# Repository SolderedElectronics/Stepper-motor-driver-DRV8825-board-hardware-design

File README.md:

# Stepper motor driver DRV8825 board Hardware Design

## About the Product

|  |
| :----------------------------------------------------------: |
| [Buy Stepper motor driver DRV8825 board](https://www.solde.red/333000) |

The stepper motor driver enables very precise control of the stepper motor. The DRV8825, located on this board, enables microstepping of a bipolar motor with an adjustable current limit, overcurrent and overtemperature protection. Controls steps up to 1/32 step. It has a potentiometer for setting the desired current.

---

## Repository Contents

This repository contains all design files for Stepper motor driver DRV8825 board, organized as follows:

- **`CAD` folder**: Contains KiCAD design files, including:
  - Schematics
  - PCB layout
  - Panel PCB layout
  - Source 3D files in Fusion360, if any
  - All files are sorted by version with a detailed change log.
- **`OUTPUTS` folder**: Includes all production-ready files, such as:
  - Bill of Materials (BOM) and interactive BOM (iBOM)
  - PDF versions of schematics
  - 3D `.step` file of the board
  - 3D-printable models
  - Gerber files for PCB manufacturing
  - Image of the pinout of the board
  - Product image
  - Compliance, legal and generic sales documents

Refer to the `Change Log` in the CAD folder for details about updates between versions.

---

## Learn More About the Product

Beyond the repository, explore the following resources:

### Soldered Verify

The **Soldered Verify** system ensures every board you purchase from Soldered is fully functional. It also provides access to exclusive test data for your product. To get started, find the unique Soldered Verify ID on your product's packaging and enter the ID on the [Soldered Verify page](https://soldered.com/verify/) to access test results and additional product details.

### Soldered Community

Soldered Community is your go-to place for technical support. Our engineers track and answer all questions posted there, and it’s a great space for the maker community. Get answers to your questions and solutions for your challenges at [Soldered Community](https://soldered.com/community).

### solde.red

solde.red is an ultimate URL shortener and information hub. Access it by typing solde.red/ followed by your product SKU, e.g., [solde.red/333000](https://solde.red/333000), to find getting-started guides, datasheets, open-source hardware and software files, certifications, images, pinouts, and more. Read more about the shortener [here](https://solde.red/info/).

---

## Contributing

Contributions are welcome! Here’s how you can get involved:

- Submit pull requests to enhance the design or fix issues.
- Report bugs or problems by opening an issue.

We encourage community collaboration to make this product even better.

---

## About Soldered

[Soldered for Makers](https://soldered.com) specializes in designing and manufacturing electronic products tailored for enthusiasts, ranging from hobbyists to professionals. Our portfolio includes electronic boards, sensors, and actuators that are widely utilized in fields such as microelectronics, mechatronics, robotics, programming, and IoT. Every product we offer is designed in-house and built upon open-source hardware and software platforms. Proudly certified and manufactured within the European Union, our catalog likely includes the product you need for your project.

We complement these products with comprehensive tutorials and manuals, product descriptions, schematics, programming codes, and project examples. Our round-the-clock [customer and technical support](https://soldered.com/community) is available for all our products, irrespective of the sales channel. Soldered’s success and services reflect our maker community’s unwavering [trust](https://www.trustpilot.com/review/soldered.com), for which we are deeply grateful. Join our community and create using Soldered products.

---

## License

All Soldered open-source hardware (OSH) is under The TAPR Open Hardware License. Read more in the LICENSE file located in this repository.

**Disclaimer:**

No warranty - all designs in this repository are distributed in the hope that they will be useful, but without any warranty. They are provided "AS IS", therefore without warranty of any kind, either expressed or implied. The entire quality and performance of what you do with the contents of this repository are your responsibility. In no event Soldered Electronics will be liable for your damages, or losses, including any general, special, incidental, or consequential damage arising out of the use or inability to use the contents of this repository. 

---

## Have fun!

Thank you for your support from your fellow makers at Soldered Electronics.

Happy Making!

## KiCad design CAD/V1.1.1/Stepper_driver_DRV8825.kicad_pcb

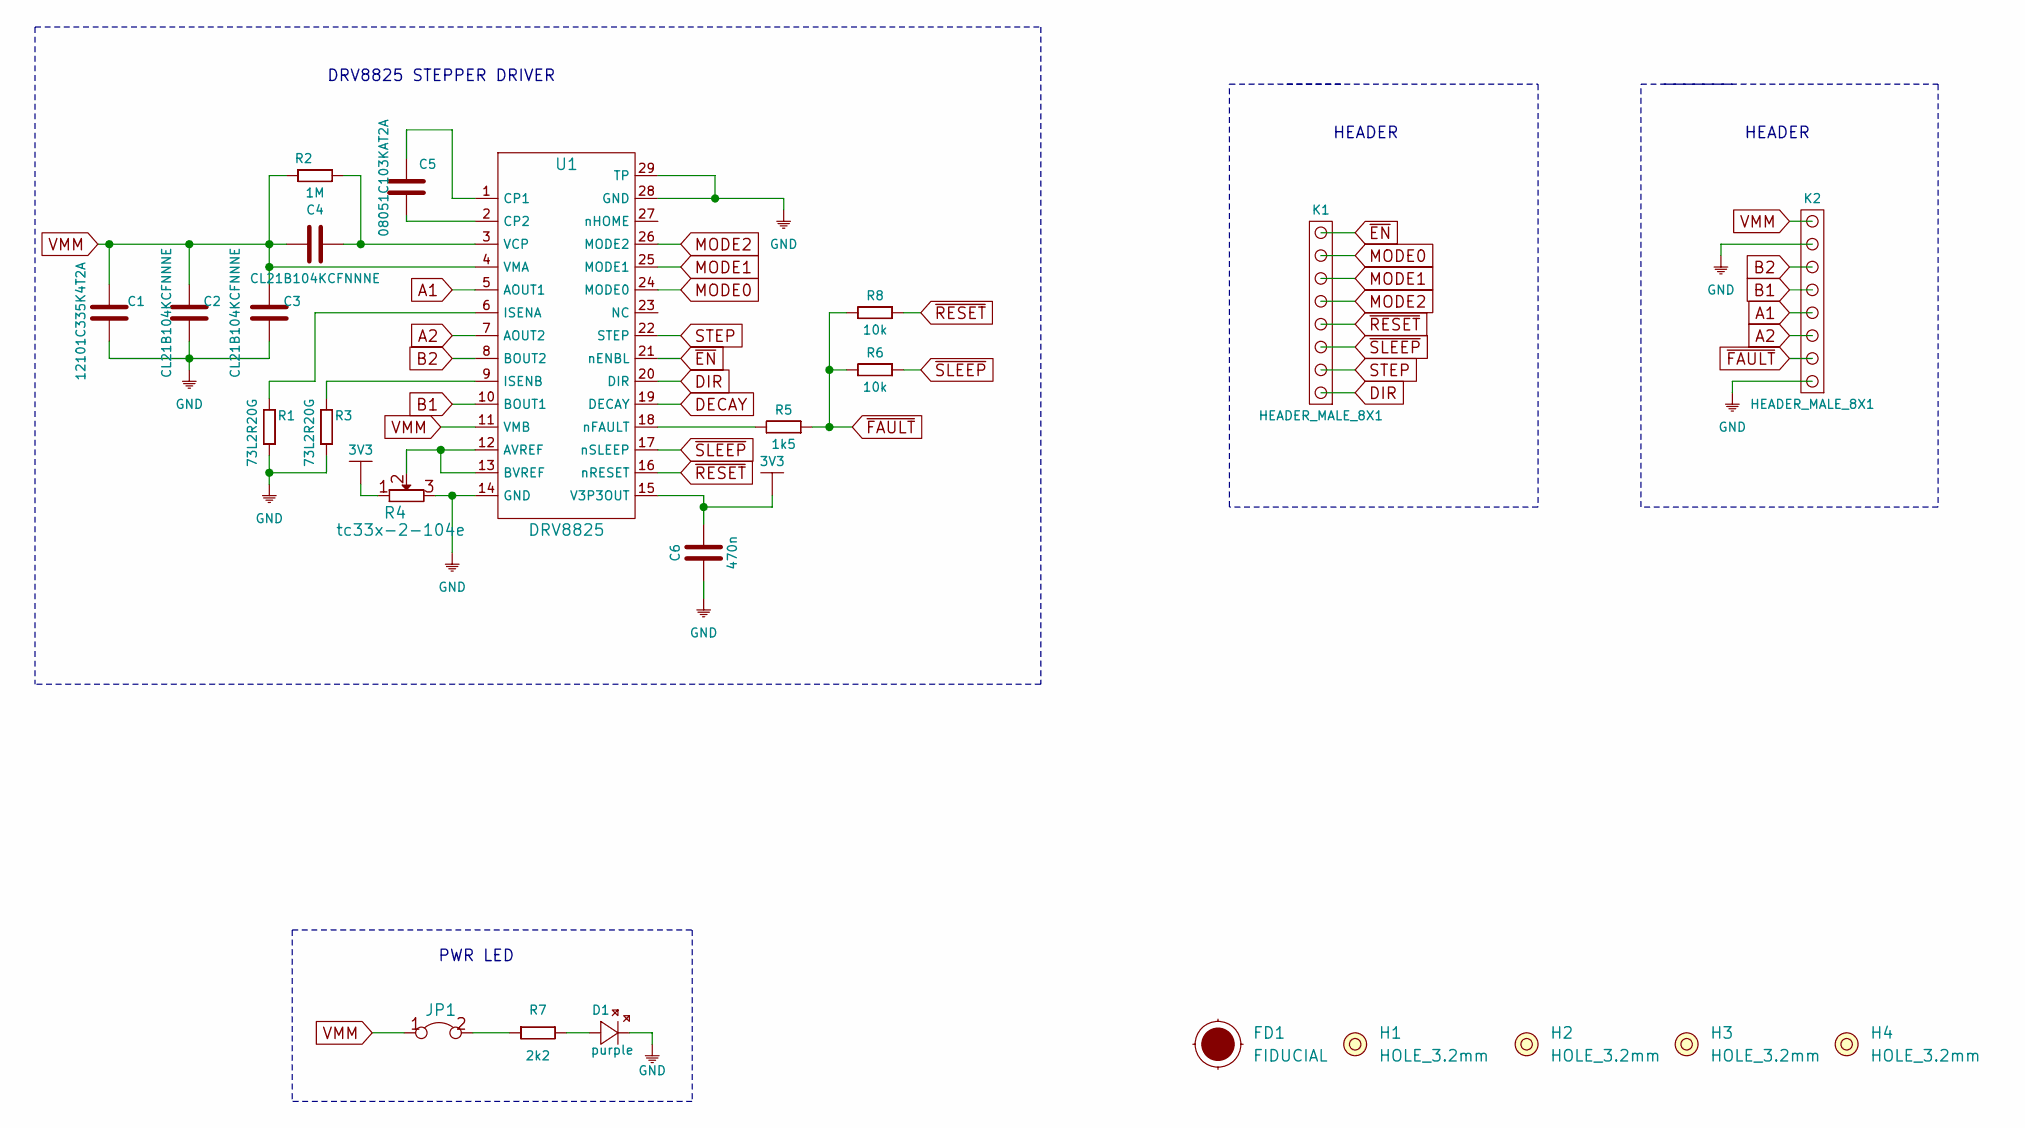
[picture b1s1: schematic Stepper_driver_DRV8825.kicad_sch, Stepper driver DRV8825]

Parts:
C1: 12101C335K4T2A; 1210C
C2, C3, C4: CL21B104KCFNNNE; 0805C
C5: 08051C103KAT2A; 0805C
C6: 470n; 0603C
D1: purple; 0402LED
FD1: FIDUCIAL; FIDUCIAL_23
H1, H2, H3, H4: HOLE_3.2mm
JP1: SMD-JUMPER-CONNECTED_TRACE_SLODERMASK
K1, K2: HEADER_MALE_8X1
R1, R3: 73L2R20G; 0603R
R2: 1M; 0603R
R4: tc33x-2-104e; tc33x-2-103e
R5: 1k5; 0603R
R6, R8: 10k; 0603R
R7: 2k2; 0402R
U1: DRV8825

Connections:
3V3: C6.2, R4.1, U1.15 (V3P3OUT)
A1: K2.4, U1.5 (AOUT1)
A2: K2.3, U1.7 (AOUT2)
B1: K2.5, U1.10 (BOUT1)
B2: K2.6, U1.8 (BOUT2)
DECAY: U1.19 (DECAY)
DIR: K1.1, U1.20 (DIR)
GND: C1.1, C2.1, C3.1, C6.1, D1.2 (K), K2.1, K2.7, R1.1, R3.1, R4.3, U1.14 (GND), U1.28 (GND), U1.29 (TP)
MODE0: K1.7, U1.24 (MODE0)
MODE1: K1.6, U1.25 (MODE1)
MODE2: K1.5, U1.26 (MODE2)
unnamed: C4.2, R2.2, U1.3 (VCP)
unnamed: C5.1, U1.2 (CP2)
unnamed: C5.2, U1.1 (CP1)
unnamed: D1.1 (A), R7.2
unnamed: JP1.2, R7.1
unnamed: R1.2, U1.6 (ISENA)
unnamed: R3.2, U1.9 (ISENB)
unnamed: R4.2, U1.12 (AVREF), U1.13 (BVREF)
unnamed: R5.2, U1.18 (nFAULT)
STEP: K1.2, U1.22 (STEP)
VMM: C1.2, C2.2, C3.2, C4.1, JP1.1, K2.8, R2.1, U1.4 (VMA), U1.11 (VMB)
~EN: K1.8, U1.21 (nENBL)
~FAULT: K2.2, R5.1, R6.2, R8.2
~RESET: K1.4, R8.1, U1.16 (nRESET)
~SLEEP: K1.3, R6.1, U1.17 (nSLEEP)

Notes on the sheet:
HEADER
DRV8825 STEPPER DRIVER
PWR LED

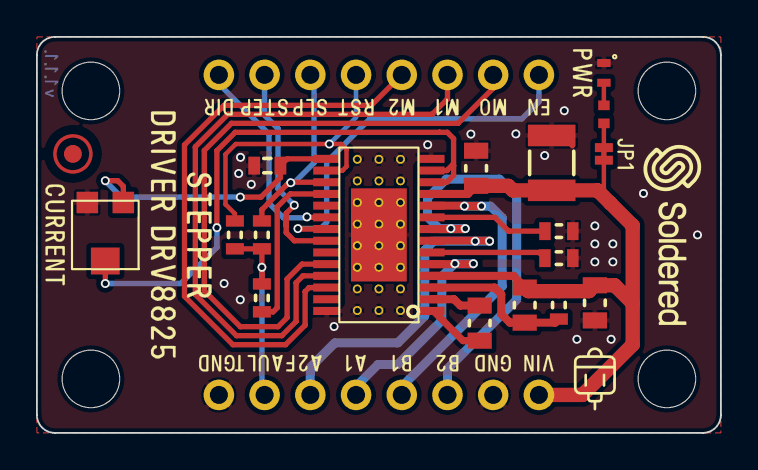
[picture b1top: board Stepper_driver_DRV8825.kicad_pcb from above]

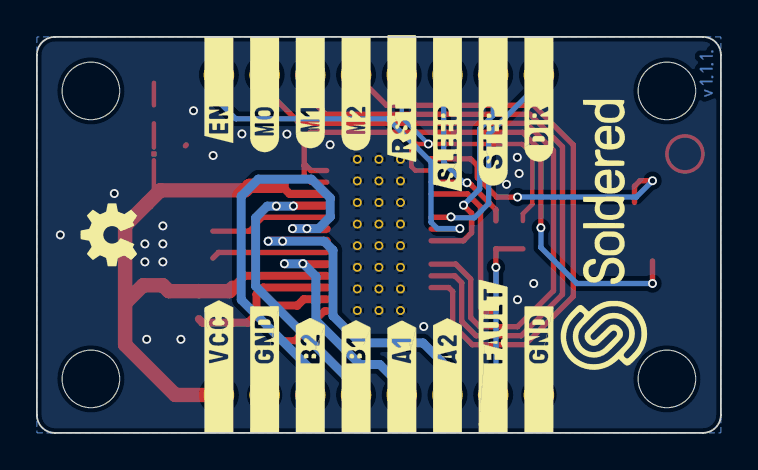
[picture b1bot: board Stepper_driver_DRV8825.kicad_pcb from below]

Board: 2 copper layers, 38.0 x 22.0 mm, 24 parts (2 on the bottom side), 25 nets.

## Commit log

2022-08-06 Updating open source files.
